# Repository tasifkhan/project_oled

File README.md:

## project_oled
- Display driver for 8x8 OLED array. Common anode setup for 64 devices, controlled by Darlington arrays and an Arduino Mega.
- Arduino code for displaying letters and numbers for the array, also a seven segment display.

### notes
- 2017_08_27 second round of cleaning. If you plan to use this design, DO NOT connect pin 10 of the Darlington arrays, leave that pin floating.
- 2017_07_18 cleanup. Hardware works with pin 10 NC. Uploading arduino firmware for seven segment and 4x4 displays.
- 2017_07_04 remove COM to GND connection in v1 (pin 10 NC). Other than that v1 works.

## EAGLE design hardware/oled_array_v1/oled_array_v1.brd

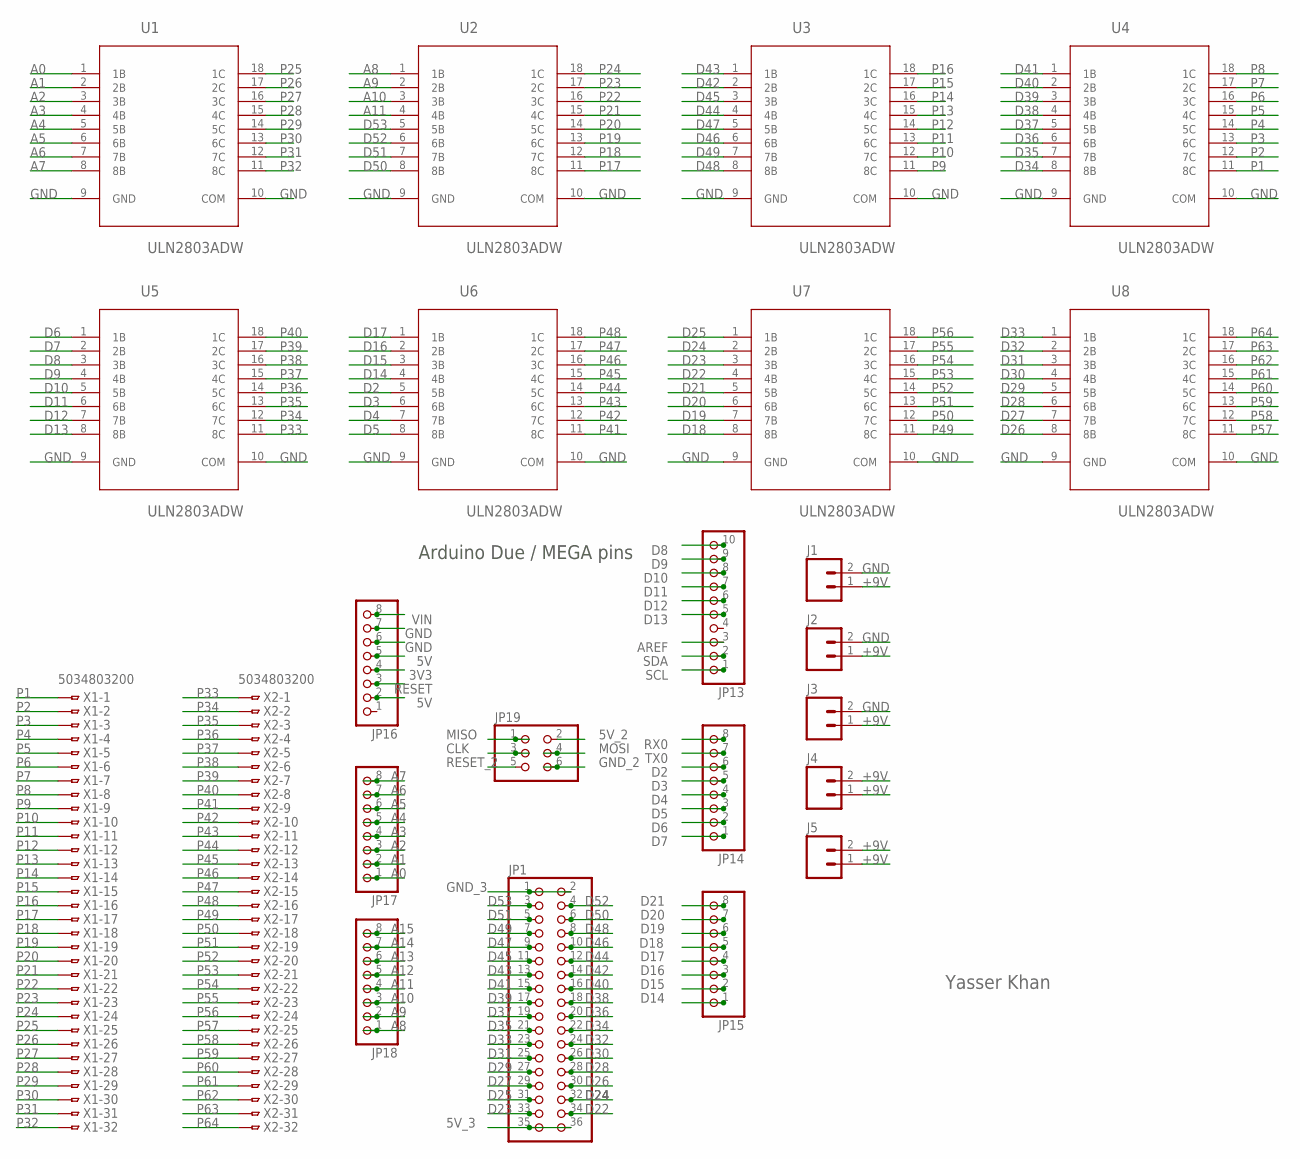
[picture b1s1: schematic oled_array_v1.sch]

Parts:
J1, J2, J3, J4, J5: M02PTH; 1X02
JP1: PINHD-2X18; 2X18
JP13: PINHD-1X10; 1X10
JP14, JP15, JP16, JP17, JP18: PINHD-1X8; 1X08
JP19: PINHD-2X3; 2X03
U1, U2, U3, U4, U5, U6, U7, U8: ULN2803ADW; SOIC127P1030X265-18N
X1, X2: 5034803200

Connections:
3V3: JP16.4
5V: JP16.2, JP16.5
5V_2: JP19.2
5V_3: JP1.35, JP1.36
+9V: J1.1, J2.1, J3.1, J4.1, J4.2, J5.1, J5.2
A0: JP17.1, U1.1 (1B)
A1: JP17.2, U1.2 (2B)
A2: JP17.3, U1.3 (3B)
A3: JP17.4, U1.4 (4B)
A4: JP17.5, U1.5 (5B)
A5: JP17.6, U1.6 (6B)
A6: JP17.7, U1.7 (7B)
A7: JP17.8, U1.8 (8B)
A8: JP18.1, U2.1 (1B)
A9: JP18.2, U2.2 (2B)
A10: JP18.3, U2.3 (3B)
A11: JP18.4, U2.4 (4B)
A12: JP18.5
A13: JP18.6
A14: JP18.7
A15: JP18.8
AREF: JP13.3
CLK: JP19.3
D2: JP14.6, U6.5 (5B)
D3: JP14.5, U6.6 (6B)
D4: JP14.4, U6.7 (7B)
D5: JP14.3, U6.8 (8B)
D6: JP14.2, U5.1 (1B)
D7: JP14.1, U5.2 (2B)
D8: JP13.10, U5.3 (3B)
D9: JP13.9, U5.4 (4B)
D10: JP13.8, U5.5 (5B)
D11: JP13.7, U5.6 (6B)
D12: JP13.6, U5.7 (7B)
D13: JP13.5, U5.8 (8B)
D14: JP15.1, U6.4 (4B)
D15: JP15.2, U6.3 (3B)
D16: JP15.3, U6.2 (2B)
D17: JP15.4, U6.1 (1B)
D18: JP15.5, U7.8 (8B)
D19: JP15.6, U7.7 (7B)
D20: JP15.7, U7.6 (6B)
D21: JP15.8, U7.5 (5B)
D22: JP1.34, U7.4 (4B)
D23: JP1.33, U7.3 (3B)
D24: JP1.32, U7.2 (2B)
D25: JP1.31, U7.1 (1B)
D26: JP1.30, U8.8 (8B)
D27: JP1.29, U8.7 (7B)
D28: JP1.28, U8.6 (6B)
D29: JP1.27, U8.5 (5B)
D30: JP1.26, U8.4 (4B)
D31: JP1.25, U8.3 (3B)
D32: JP1.24, U8.2 (2B)
D33: JP1.23, U8.1 (1B)
D34: JP1.22, U4.8 (8B)
D35: JP1.21, U4.7 (7B)
D36: JP1.20, U4.6 (6B)
D37: JP1.19, U4.5 (5B)
D38: JP1.18, U4.4 (4B)
D39: JP1.17, U4.3 (3B)
D40: JP1.16, U4.2 (2B)
D41: JP1.15, U4.1 (1B)
D42: JP1.14, U3.2 (2B)
D43: JP1.13, U3.1 (1B)
D44: JP1.12, U3.4 (4B)
D45: JP1.11, U3.3 (3B)
D46: JP1.10, U3.6 (6B)
D47: JP1.9, U3.5 (5B)
D48: JP1.8, U3.8 (8B)
D49: JP1.7, U3.7 (7B)
D50: JP1.6, U2.8 (8B)
D51: JP1.5, U2.7 (7B)
D52: JP1.4, U2.6 (6B)
D53: JP1.3, U2.5 (5B)
GND: J1.2, J2.2, J3.2, JP16.6, JP16.7, U1.9 (GND), U1.10 (COM), U2.9 (GND), U2.10 (COM), U3.9 (GND), U3.10 (COM), U4.9 (GND), U4.10 (COM), U5.9 (GND), U5.10 (COM), U6.9 (GND), U6.10 (COM), U7.9 (GND), U7.10 (COM), U8.9 (GND), U8.10 (COM)
GND_2: JP19.6
GND_3: JP1.1, JP1.2
MISO: JP19.1
MOSI: JP19.4
P1: U4.11 (8C), X1.1
P2: U4.12 (7C), X1.2
P3: U4.13 (6C), X1.3
P4: U4.14 (5C), X1.4
P5: U4.15 (4C), X1.5
P6: U4.16 (3C), X1.6
P7: U4.17 (2C), X1.7
P8: U4.18 (1C), X1.8
P9: U3.11 (8C), X1.9
P10: U3.12 (7C), X1.10
P11: U3.13 (6C), X1.11
P12: U3.14 (5C), X1.12
P13: U3.15 (4C), X1.13
P14: U3.16 (3C), X1.14
P15: U3.17 (2C), X1.15
P16: U3.18 (1C), X1.16
P17: U2.11 (8C), X1.17
P18: U2.12 (7C), X1.18
P19: U2.13 (6C), X1.19
P20: U2.14 (5C), X1.20
P21: U2.15 (4C), X1.21
P22: U2.16 (3C), X1.22
P23: U2.17 (2C), X1.23
P24: U2.18 (1C), X1.24
P25: U1.18 (1C), X1.25
P26: U1.17 (2C), X1.26
P27: U1.16 (3C), X1.27
P28: U1.15 (4C), X1.28
P29: U1.14 (5C), X1.29
P30: U1.13 (6C), X1.30
P31: U1.12 (7C), X1.31
P32: U1.11 (8C), X1.32
P33: U5.11 (8C), X2.1
P34: U5.12 (7C), X2.2
P35: U5.13 (6C), X2.3
P36: U5.14 (5C), X2.4
P37: U5.15 (4C), X2.5
P38: U5.16 (3C), X2.6
P39: U5.17 (2C), X2.7
P40: U5.18 (1C), X2.8
P41: U6.11 (8C), X2.9
P42: U6.12 (7C), X2.10
P43: U6.13 (6C), X2.11
P44: U6.14 (5C), X2.12
P45: U6.15 (4C), X2.13
P46: U6.16 (3C), X2.14
P47: U6.17 (2C), X2.15
P48: U6.18 (1C), X2.16
P49: U7.11 (8C), X2.17
P50: U7.12 (7C), X2.18
P51: U7.13 (6C), X2.19
P52: U7.14 (5C), X2.20
P53: U7.15 (4C), X2.21
P54: U7.16 (3C), X2.22
P55: U7.17 (2C), X2.23
P56: U7.18 (1C), X2.24
P57: U8.11 (8C), X2.25
P58: U8.12 (7C), X2.26
P59: U8.13 (6C), X2.27
P60: U8.14 (5C), X2.28
P61: U8.15 (4C), X2.29
P62: U8.16 (3C), X2.30
P63: U8.17 (2C), X2.31
P64: U8.18 (1C), X2.32
RESET: JP16.3
RESET_2: JP19.5
RX0: JP14.8
SCL: JP13.1
SDA: JP13.2
TX0: JP14.7
VIN: JP16.8

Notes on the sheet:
Arduino Due / MEGA pins
Yasser Khan

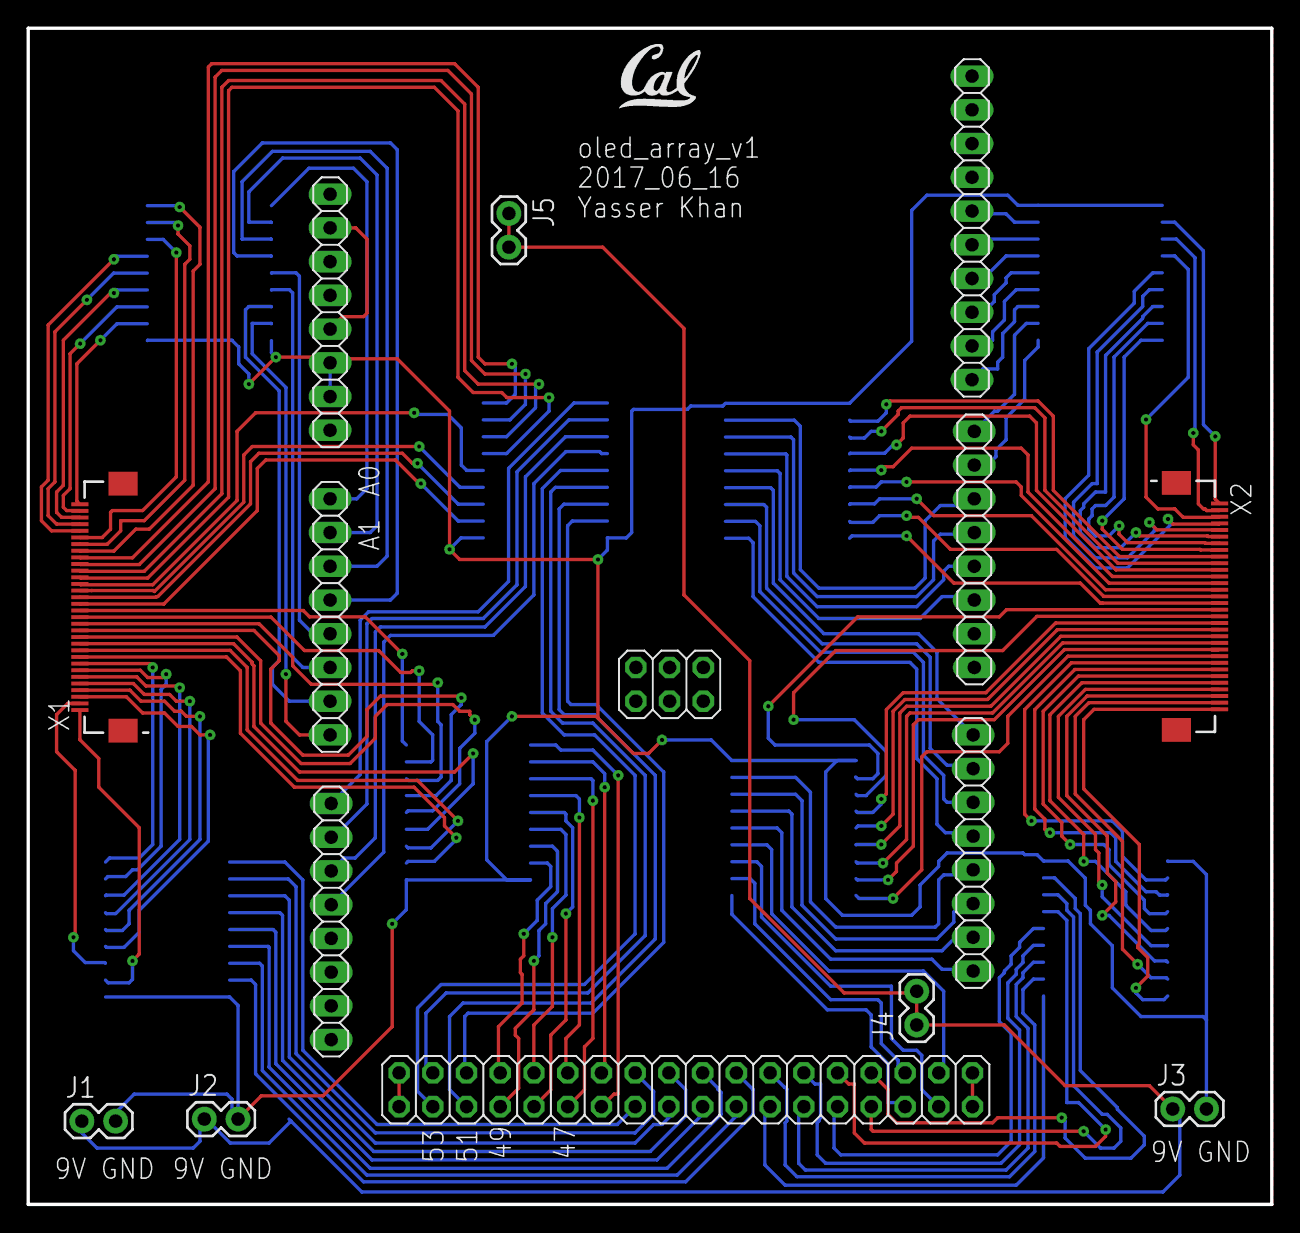
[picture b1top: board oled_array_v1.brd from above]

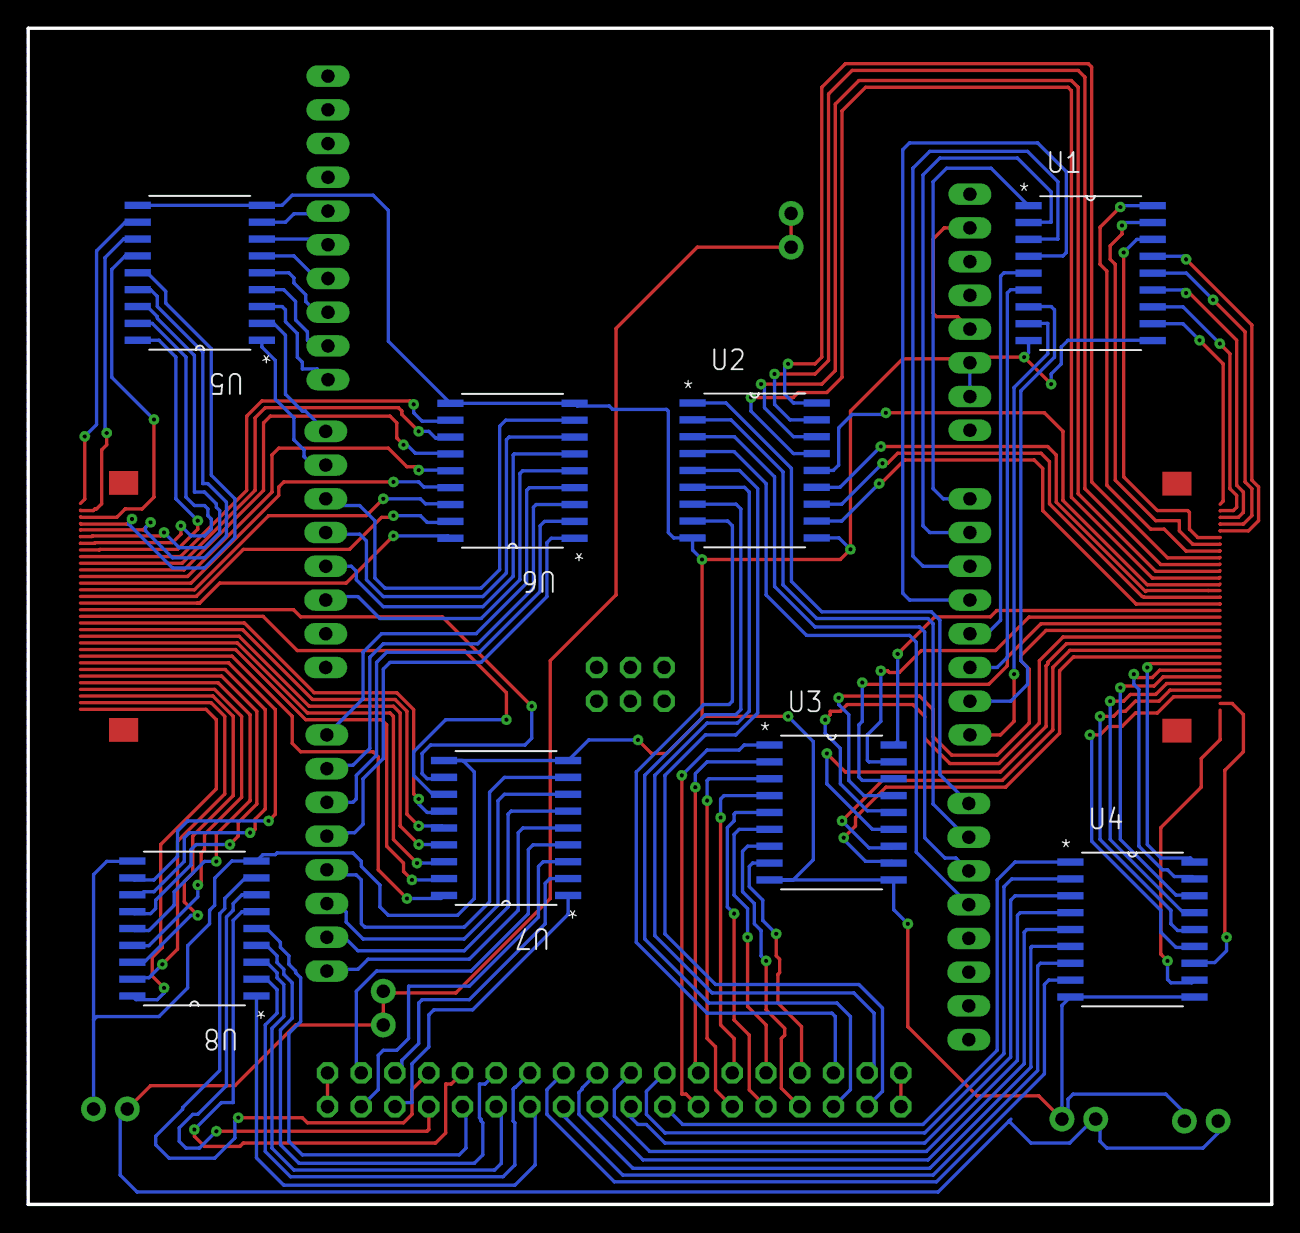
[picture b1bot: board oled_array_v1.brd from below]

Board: 2 copper layers, 93.6 x 88.6 mm, 23 parts (8 on the bottom side), 133 nets.

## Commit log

2017-06-16 Initial commit.
2017-06-16 pinout added
2017-07-18 firmware added
2017-07-18 clean update 2017_07_18 hardware and firmware are working
2017-08-27 second round of cleaning
2017-09-13 moved directory to the paper folder

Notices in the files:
parts and their libraries:
SparkFun-Connectors: Licensing: Creative Commons ShareAlike 4.0 International - https://creativecommons.org/licenses/by-sa/4.0
